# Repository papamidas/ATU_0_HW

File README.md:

# ATU_0_HW

Antenna Tuning Unit for Radio Amateurs:

- LC- or CL-type antenna tuner, software selectable
- 256 capacitance values: 0..2.5 nF in steps of 10 pF
- 256 inductance values	- 256 inductance values: 0..15 µH in steps of 60 nH
- controlled by an Arduino Nano
- powered by a USB power bank
- low current consumption (25..45 mA) by using bistable relays
- remote control via Bluetooth
- simple user interface using the Android app "serial bluetooth terminal"
- 10 memory buttons for recalling setups for different frequency bands
- open source hardware, open source firmware

have fun!
73
papamidas (DM1CR)

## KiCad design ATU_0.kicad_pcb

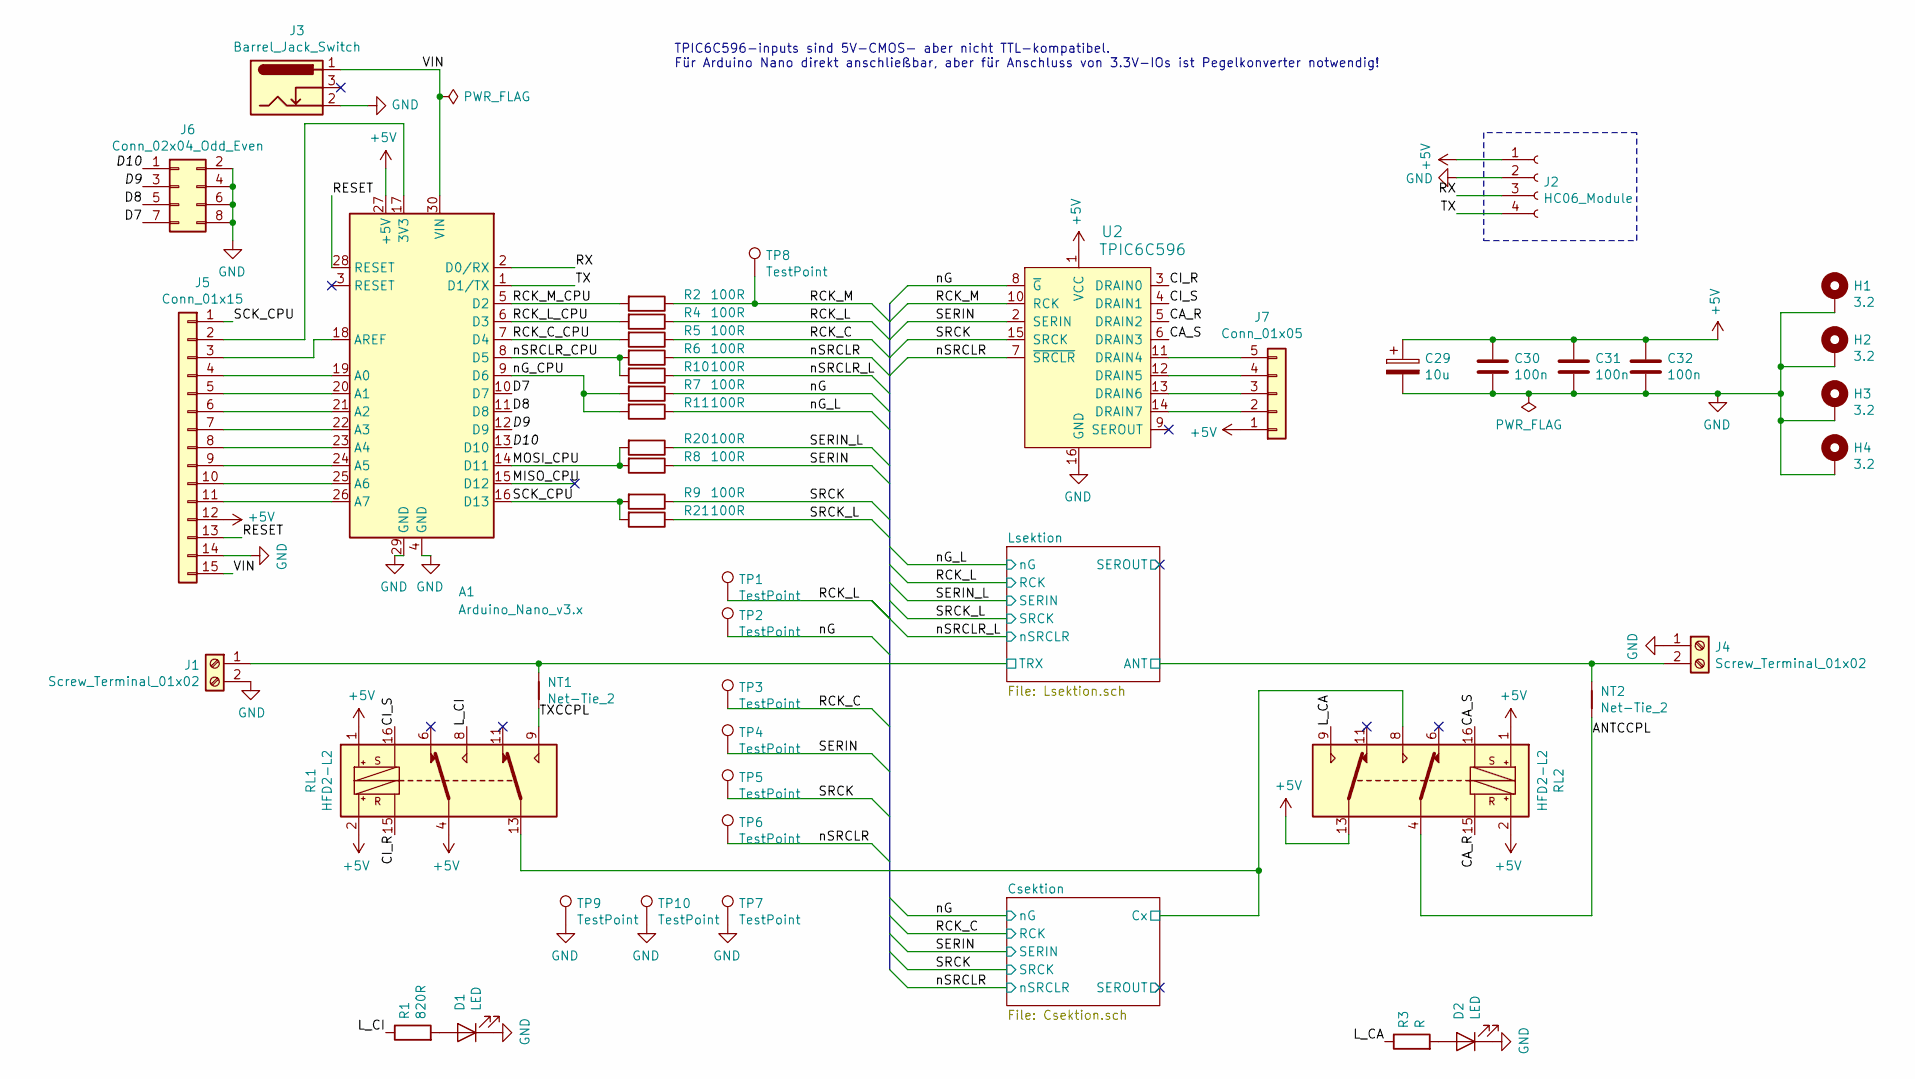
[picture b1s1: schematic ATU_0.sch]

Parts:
A1: Arduino_Nano_v3.x; Arduino_Nano_WithMountingHoles
C29: 10u; CP_Tantalum_Case-C_EIA-6032-28_Hand
C30, C31, C32: 100n; C_0805_HandSoldering
D1, D2: LED; D_0805
H1, H2, H3, H4: 3.2; MountingHole_3.2mm_M3_DIN965_Pad
J1, J4: Screw_Terminal_01x02; TerminalBlock_bornier-2_P5.08mm
J2: HC06_Module; Socket_Strip_Straight_1x04_Pitch2.54mm
J3: Barrel_Jack_Switch; Barrel_Jack_5.5mmODx2.1mmID_PJ-202A
J5: Conn_01x15; PinHeader_1x15_P2.54mm_Vertical
J6: Conn_02x04_Odd_Even; PinHeader_2x04_P2.54mm_Vertical
J7: Conn_01x05; PinHeader_1x05_P2.54mm_Vertical
NT1, NT2: Net-Tie_2; NetTie-2_SMD_Pad2.0mm
R1: 820R; R_0805_HandSoldering
R2, R4, R5, R6, R7, R8, R9, R10, R11, R20, R21: 100R; R_0805_HandSoldering
R3: R; R_0805_HandSoldering
RL1, RL2: HFD2-L2
TP1, TP2, TP3, TP4, TP5, TP6, TP7, TP8, TP9, TP10: TestPoint; PinHeader_1x01_P2.54mm_Vertical
U2: TPIC6C596; SOIC-16_W3.90mm; MPN TPIC6C596; Digi-Key_PN Mouser TPIC6C596DRQ1

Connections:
+5V: A1.27 (+5V), C29.1, C30.1, C31.1, C32.1, J2.1, J5.12, J7.1, RL1.1, RL1.2, RL1.4, RL2.1, RL2.2, RL2.13, U2.1 (VCC); also elsewhere on the board
/ANTCCPL: NT2.2, RL2.4
/CA_R: RL2.15, U2.5 (DRAIN2)
/CA_S: RL2.16, U2.6 (DRAIN3)
/CI_R: RL1.15, U2.3 (DRAIN0)
/CI_S: RL1.16, U2.4 (DRAIN1)
/Csektion/Cx: RL1.13, RL2.8; also elsewhere on the board
/D7: A1.10 (D7), J6.7
/D8: A1.11 (D8), J6.5
/D9: A1.12 (D9), J6.3
/D10: A1.13 (D10), J6.1
/L_CA: R3.1, RL2.9
/L_CI: R1.1, RL1.8
/Lsektion/ANT: J4.2, NT2.1; also elsewhere on the board
/Lsektion/TRX: J1.1, NT1.1; also elsewhere on the board
/MISO_CPU: A1.15 (D12)
/MOSI_CPU: A1.14 (D11), R8.2, R20.2
/RCK_C: R5.1, TP3.1; also elsewhere on the board
/RCK_C_CPU: A1.7 (D4), R5.2
/RCK_L: R4.1, TP1.1; also elsewhere on the board
/RCK_L_CPU: A1.6 (D3), R4.2
/RCK_M: R2.1, TP8.1, U2.10 (RCK)
/RCK_M_CPU: A1.5 (D2), R2.2
/RESET: A1.28 (RESET), J5.13
/RX: A1.2 (D0/RX), J2.3
/SCK_CPU: A1.16 (D13), J5.1, R9.2, R21.2
/SERIN: R8.1, TP4.1, U2.2 (SERIN); also elsewhere on the board
/SERIN_L: R20.1; also elsewhere on the board
/SRCK: R9.1, TP5.1, U2.15 (SRCK); also elsewhere on the board
/SRCK_L: R21.1; also elsewhere on the board
/TX: A1.1 (D1/TX), J2.4
/TXCCPL: NT1.2, RL1.9
/VIN: A1.30 (VIN), J3.1, J5.15
/nG: R7.1, TP2.1, U2.8 (~G); also elsewhere on the board
/nG_CPU: A1.9 (D6), R7.2, R11.2
/nG_L: R11.1; also elsewhere on the board
/nSRCLR: R6.1, TP6.1, U2.7 (~SRCLR); also elsewhere on the board
/nSRCLR_CPU: A1.8 (D5), R6.2, R10.2
/nSRCLR_L: R10.1; also elsewhere on the board
GND: A1.4 (GND), A1.29 (GND), C29.2, C30.2, C31.2, C32.2, D1.1 (K), D2.1 (K), H1.1, H2.1, H3.1, H4.1, J1.2, J2.2, J3.2, J4.1, J5.14, J6.2, J6.4, J6.6, J6.8, TP7.1, TP9.1, TP10.1, U2.16 (GND); also elsewhere on the board
unnamed: A1.17 (3V3), J5.2
unnamed: A1.18 (AREF), J5.3
unnamed: A1.19 (A0), J5.4
unnamed: A1.20 (A1), J5.5
unnamed: A1.21 (A2), J5.6
unnamed: A1.22 (A3), J5.7
unnamed: A1.23 (A4), J5.8
unnamed: A1.24 (A5), J5.9
unnamed: A1.25 (A6), J5.10
unnamed: A1.26 (A7), J5.11
unnamed: D1.2 (A), R1.2
unnamed: D2.2 (A), R3.2
unnamed: J7.2, U2.14 (DRAIN7)
unnamed: J7.3, U2.13 (DRAIN6)
unnamed: J7.4, U2.12 (DRAIN5)
unnamed: J7.5, U2.11 (DRAIN4)

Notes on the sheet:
TPIC6C596-inputs sind 5V-CMOS- aber nicht TTL-kompatibel. Für Arduino Nano direkt anschließbar, aber für Anschluss von 3.3V-IOs ist Pegelkonverter notwendig!

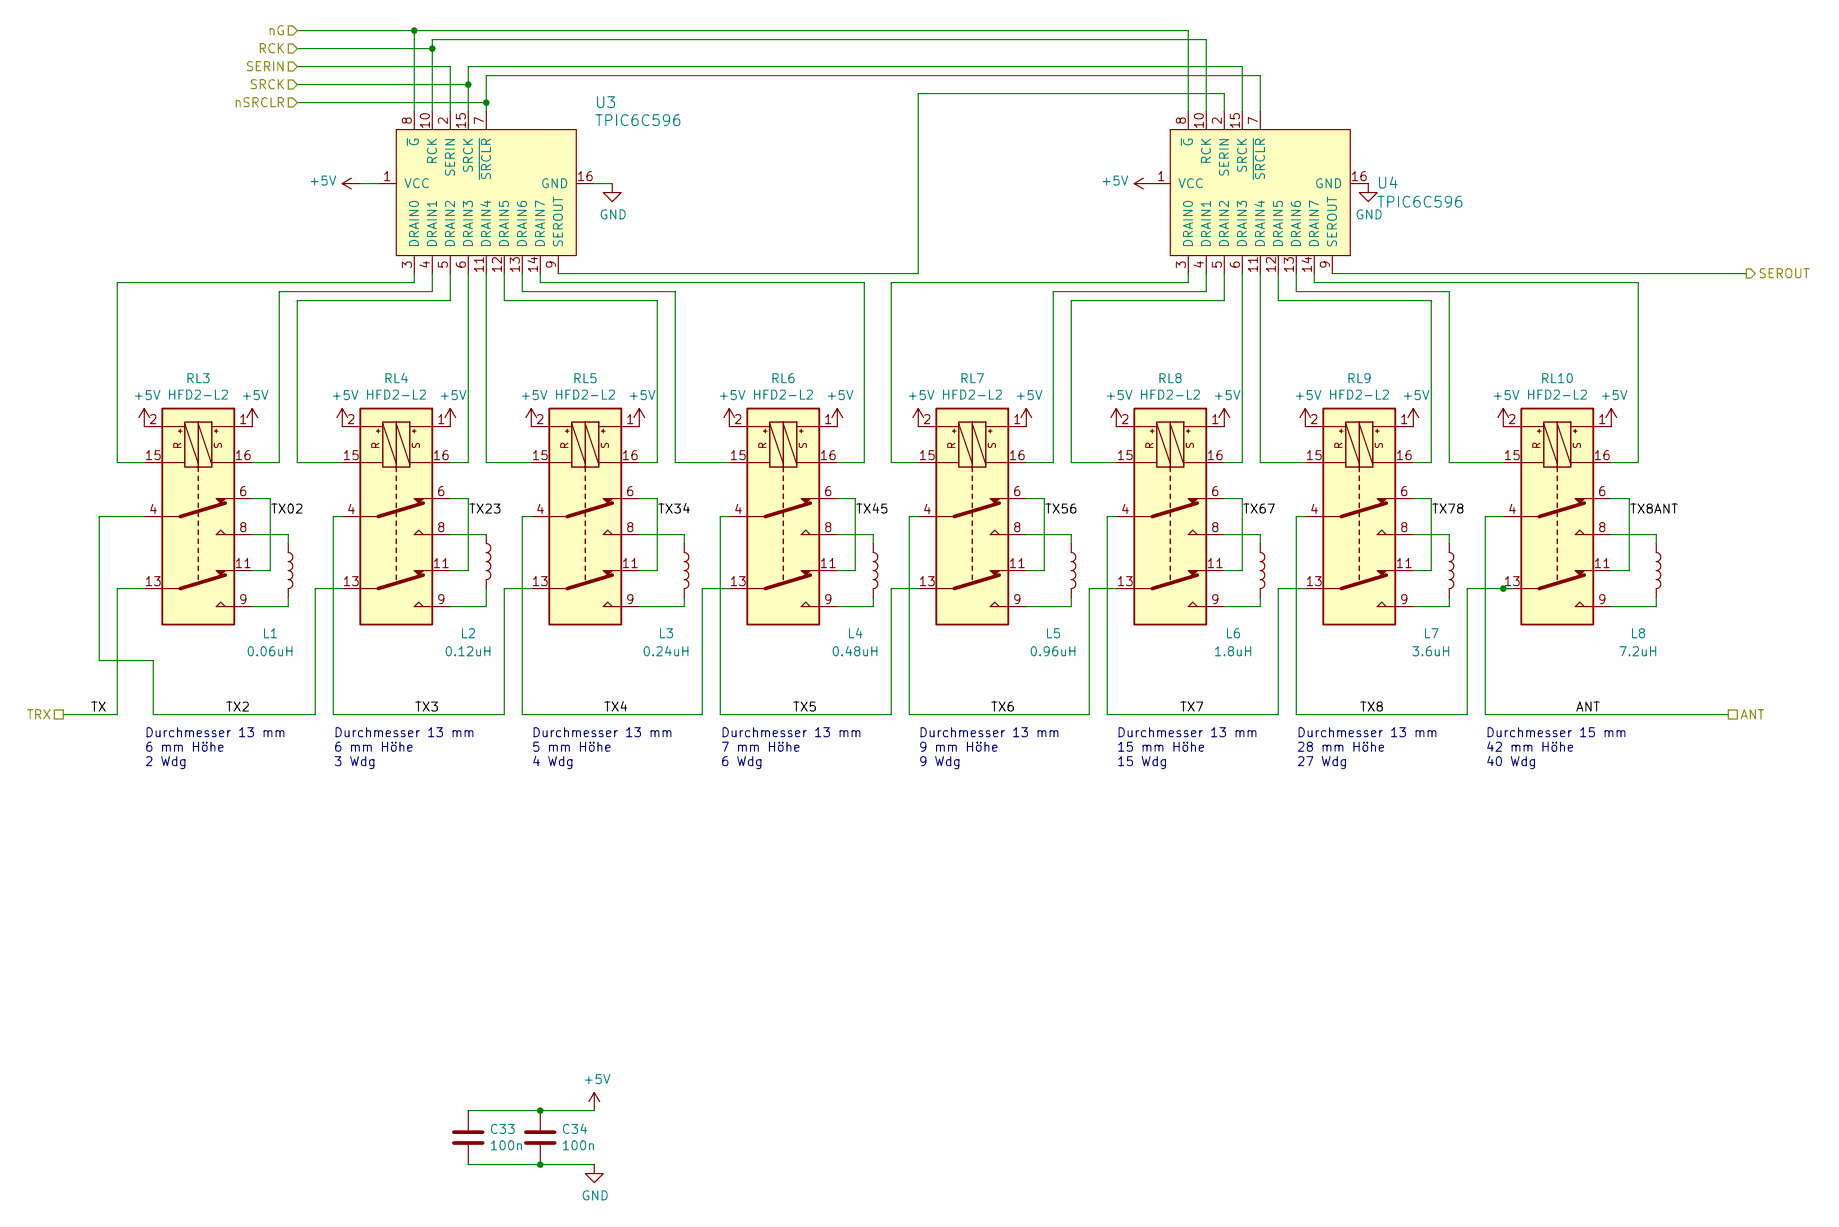
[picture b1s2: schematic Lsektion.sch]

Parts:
C33, C34: 100n; C_0805_HandSoldering
L1: 0.06uH; Aircoil_7_62_d15
L2: 0.12uH; Aircoil_7_62_d15
L3: 0.24uH; Aircoil_7_62_d15
L4: 0.48uH; Aircoil_7_62_d15
L5: 0.96uH; Aircoil_10_16_d15
L6: 1.8uH; Aircoil_15_24_d15
L7: 3.6uH; Aircoil_27_94_d15
L8: 7.2uH; Aircoil_43_18_d17
RL3, RL4, RL5, RL6, RL7, RL8, RL9, RL10: HFD2-L2
U3, U4: TPIC6C596; SOIC-16_W3.90mm; MPN TPIC6C596; Digi-Key_PN Mouser TPIC6C596DRQ1

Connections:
+5V: C33.1, C34.1, RL3.1, RL3.2, RL4.1, RL4.2, RL5.1, RL5.2, RL6.1, RL6.2, RL7.1, RL7.2, RL8.1, RL8.2, RL9.1, RL9.2, RL10.1, RL10.2, U3.1 (VCC), U4.1 (VCC); also elsewhere on the board
/Lsektion/ANT: RL10.4; also elsewhere on the board
/Lsektion/SEROUT: U4.9 (SEROUT)
/Lsektion/TRX: RL3.13; also elsewhere on the board
/Lsektion/TX2: RL3.4, RL4.13
/Lsektion/TX02: RL3.6, RL3.11
/Lsektion/TX3: RL4.4, RL5.13
/Lsektion/TX4: RL5.4, RL6.13
/Lsektion/TX5: RL6.4, RL7.13
/Lsektion/TX6: RL7.4, RL8.13
/Lsektion/TX7: RL8.4, RL9.13
/Lsektion/TX8: RL9.4, RL10.13
/Lsektion/TX8ANT: RL10.6, RL10.11
/Lsektion/TX23: RL4.6, RL4.11
/Lsektion/TX34: RL5.6, RL5.11
/Lsektion/TX45: RL6.6, RL6.11
/Lsektion/TX56: RL7.6, RL7.11
/Lsektion/TX67: RL8.6, RL8.11
/Lsektion/TX78: RL9.6, RL9.11
/RCK_L: U3.10 (RCK), U4.10 (RCK); also elsewhere on the board
/SERIN_L: U3.2 (SERIN); also elsewhere on the board
/SRCK_L: U3.15 (SRCK), U4.15 (SRCK); also elsewhere on the board
/nG_L: U3.8 (~G), U4.8 (~G); also elsewhere on the board
/nSRCLR_L: U3.7 (~SRCLR), U4.7 (~SRCLR); also elsewhere on the board
GND: C33.2, C34.2, U3.16 (GND), U4.16 (GND); also elsewhere on the board
unnamed: L1.1, RL3.8
unnamed: L1.2, RL3.9
unnamed: L2.1, RL4.8
unnamed: L2.2, RL4.9
unnamed: L3.1, RL5.8
unnamed: L3.2, RL5.9
unnamed: L4.1, RL6.8
unnamed: L4.2, RL6.9
unnamed: L5.1, RL7.8
unnamed: L5.2, RL7.9
unnamed: L6.1, RL8.8
unnamed: L6.2, RL8.9
unnamed: L7.1, RL9.8
unnamed: L7.2, RL9.9
unnamed: L8.1, RL10.8
unnamed: L8.2, RL10.9
unnamed: RL3.15, U3.3 (DRAIN0)
unnamed: RL3.16, U3.4 (DRAIN1)
unnamed: RL4.15, U3.5 (DRAIN2)
unnamed: RL4.16, U3.6 (DRAIN3)
unnamed: RL5.15, U3.11 (DRAIN4)
unnamed: RL5.16, U3.12 (DRAIN5)
unnamed: RL6.15, U3.13 (DRAIN6)
unnamed: RL6.16, U3.14 (DRAIN7)
unnamed: RL7.15, U4.3 (DRAIN0)
unnamed: RL7.16, U4.4 (DRAIN1)
unnamed: RL8.15, U4.5 (DRAIN2)
unnamed: RL8.16, U4.6 (DRAIN3)
unnamed: RL9.15, U4.11 (DRAIN4)
unnamed: RL9.16, U4.12 (DRAIN5)
unnamed: RL10.15, U4.13 (DRAIN6)
unnamed: RL10.16, U4.14 (DRAIN7)
unnamed: U3.9 (SEROUT), U4.2 (SERIN)

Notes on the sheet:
Durchmesser 13 mm 6 mm Höhe 2 Wdg
Durchmesser 13 mm 6 mm Höhe 3 Wdg
Durchmesser 13 mm 5 mm Höhe 4 Wdg
Durchmesser 13 mm 7 mm Höhe 6 Wdg
Durchmesser 13 mm 9 mm Höhe 9 Wdg
Durchmesser 13 mm 15 mm Höhe 15 Wdg
Durchmesser 13 mm 28 mm Höhe 27 Wdg
Durchmesser 15 mm 42 mm Höhe 40 Wdg

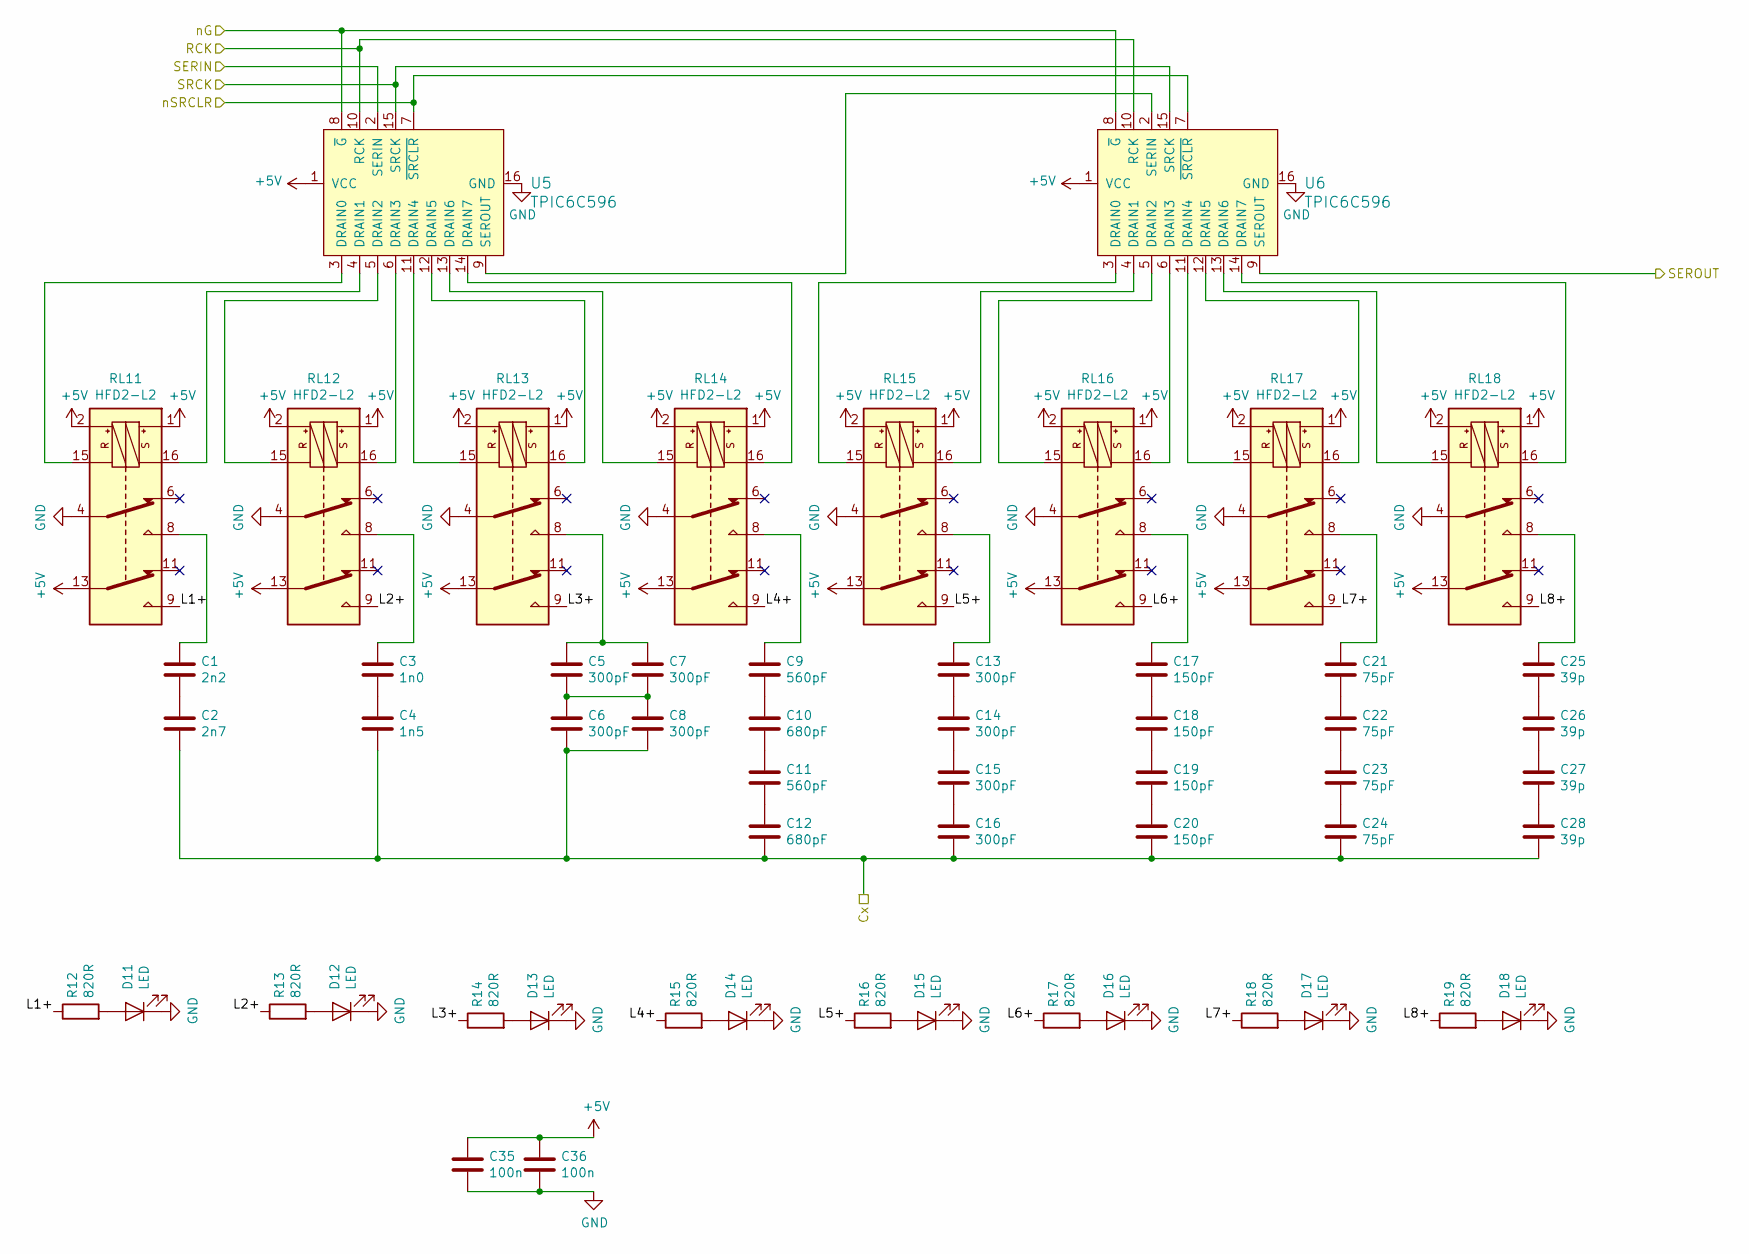
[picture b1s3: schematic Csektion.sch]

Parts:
C1: 2n2; C_1210_HandSoldering
C2: 2n7; C_1210_HandSoldering
C3: 1n0; C_1210_HandSoldering
C4: 1n5; C_1210_HandSoldering
C5, C6, C7, C8, C13, C14, C15, C16: 300pF; C_1210_HandSoldering
C9, C11: 560pF; C_1210_HandSoldering
C10, C12: 680pF; C_1210_HandSoldering
C17, C18, C19, C20: 150pF; C_1210_HandSoldering
C21, C22, C23, C24: 75pF; C_1210_HandSoldering
C25, C26, C27, C28: 39p; C_1210_HandSoldering
C35, C36: 100n; C_0805_HandSoldering
D11, D12, D13, D14, D15, D16, D17, D18: LED; D_0805
R12, R13, R14, R15, R16, R17, R18, R19: 820R; R_0805_HandSoldering
RL11, RL12, RL13, RL14, RL15, RL16, RL17, RL18: HFD2-L2
U5, U6: TPIC6C596; SOIC-16_W3.90mm; MPN TPIC6C596; Digi-Key_PN Mouser TPIC6C596DRQ1

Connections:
+5V: C35.1, C36.1, RL11.1, RL11.2, RL11.13, RL12.1, RL12.2, RL12.13, RL13.1, RL13.2, RL13.13, RL14.1, RL14.2, RL14.13, RL15.1, RL15.2, RL15.13, RL16.1, RL16.2, RL16.13, RL17.1, RL17.2, RL17.13, RL18.1, RL18.2, RL18.13, U5.1 (VCC), U6.1 (VCC); also elsewhere on the board
/Csektion/Cx: C2.2, C4.2, C6.2, C8.2, C12.2, C16.2, C20.2, C24.2, C28.2; also elsewhere on the board
/Csektion/L1+: R12.1, RL11.9
/Csektion/L2+: R13.1, RL12.9
/Csektion/L3+: R14.1, RL13.9
/Csektion/L4+: R15.1, RL14.9
/Csektion/L5+: R16.1, RL15.9
/Csektion/L6+: R17.1, RL16.9
/Csektion/L7+: R18.1, RL17.9
/Csektion/L8+: R19.1, RL18.9
/Csektion/SEROUT: U6.9 (SEROUT)
/RCK_C: U5.10 (RCK), U6.10 (RCK); also elsewhere on the board
/SERIN: U5.2 (SERIN); also elsewhere on the board
/SRCK: U5.15 (SRCK), U6.15 (SRCK); also elsewhere on the board
/nG: U5.8 (~G), U6.8 (~G); also elsewhere on the board
/nSRCLR: U5.7 (~SRCLR), U6.7 (~SRCLR); also elsewhere on the board
GND: C35.2, C36.2, D11.1 (K), D12.1 (K), D13.1 (K), D14.1 (K), D15.1 (K), D16.1 (K), D17.1 (K), D18.1 (K), RL11.4, RL12.4, RL13.4, RL14.4, RL15.4, RL16.4, RL17.4, RL18.4, U5.16 (GND), U6.16 (GND); also elsewhere on the board
unnamed: C1.1, RL11.8
unnamed: C1.2, C2.1
unnamed: C3.1, RL12.8
unnamed: C3.2, C4.1
unnamed: C5.1, C7.1, RL13.8
unnamed: C5.2, C6.1, C7.2, C8.1
unnamed: C9.1, RL14.8
unnamed: C9.2, C10.1
unnamed: C10.2, C11.1
unnamed: C11.2, C12.1
unnamed: C13.1, RL15.8
unnamed: C13.2, C14.1
unnamed: C14.2, C15.1
unnamed: C15.2, C16.1
unnamed: C17.1, RL16.8
unnamed: C17.2, C18.1
unnamed: C18.2, C19.1
unnamed: C19.2, C20.1
unnamed: C21.1, RL17.8
unnamed: C21.2, C22.1
unnamed: C22.2, C23.1
unnamed: C23.2, C24.1
unnamed: C25.1, RL18.8
unnamed: C25.2, C26.1
unnamed: C26.2, C27.1
unnamed: C27.2, C28.1
unnamed: D11.2 (A), R12.2
unnamed: D12.2 (A), R13.2
unnamed: D13.2 (A), R14.2
unnamed: D14.2 (A), R15.2
unnamed: D15.2 (A), R16.2
unnamed: D16.2 (A), R17.2
unnamed: D17.2 (A), R18.2
unnamed: D18.2 (A), R19.2
unnamed: RL11.15, U5.3 (DRAIN0)
unnamed: RL11.16, U5.4 (DRAIN1)
unnamed: RL12.15, U5.5 (DRAIN2)
unnamed: RL12.16, U5.6 (DRAIN3)
unnamed: RL13.15, U5.11 (DRAIN4)
unnamed: RL13.16, U5.12 (DRAIN5)
unnamed: RL14.15, U5.13 (DRAIN6)
unnamed: RL14.16, U5.14 (DRAIN7)
unnamed: RL15.15, U6.3 (DRAIN0)
unnamed: RL15.16, U6.4 (DRAIN1)
unnamed: RL16.15, U6.5 (DRAIN2)
unnamed: RL16.16, U6.6 (DRAIN3)
unnamed: RL17.15, U6.11 (DRAIN4)
unnamed: RL17.16, U6.12 (DRAIN5)
unnamed: RL18.15, U6.13 (DRAIN6)
unnamed: RL18.16, U6.14 (DRAIN7)
unnamed: U5.9 (SEROUT), U6.2 (SERIN)

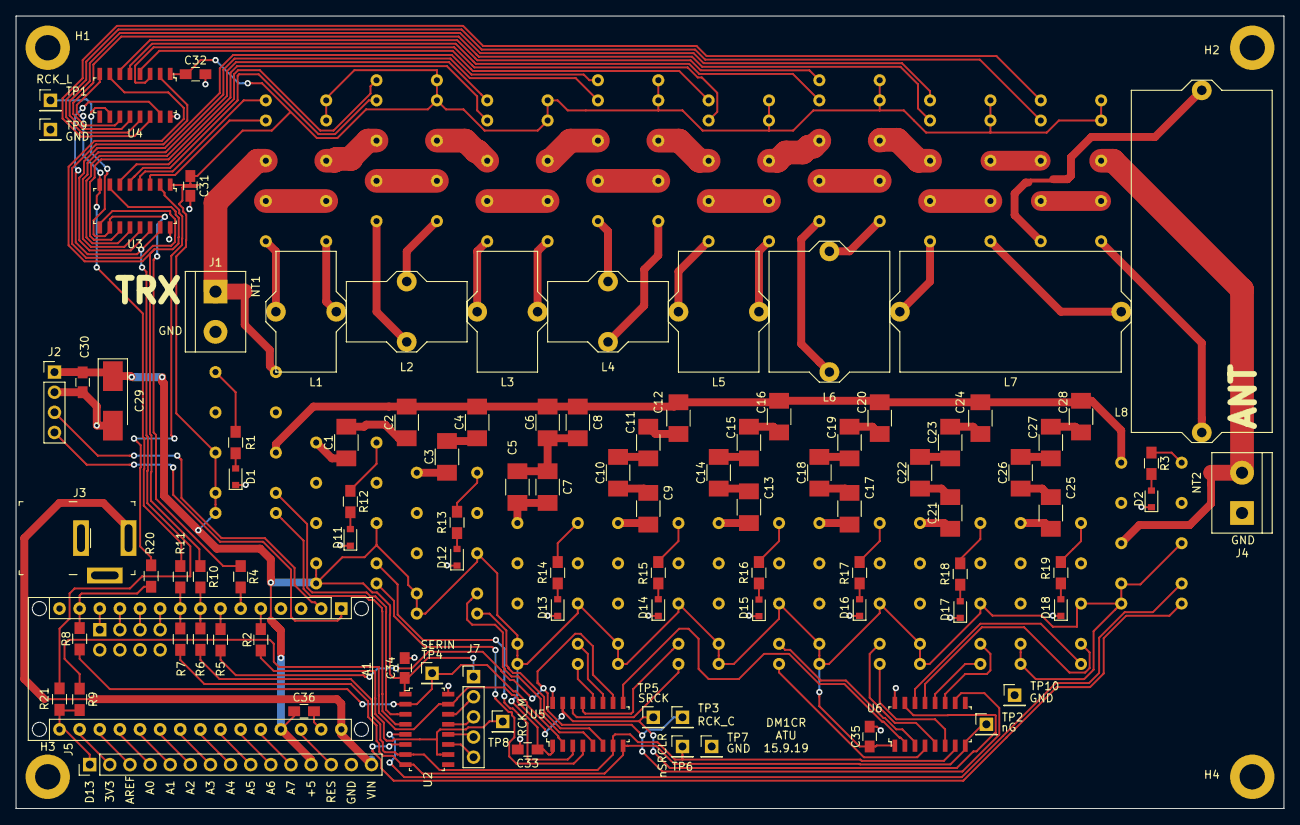
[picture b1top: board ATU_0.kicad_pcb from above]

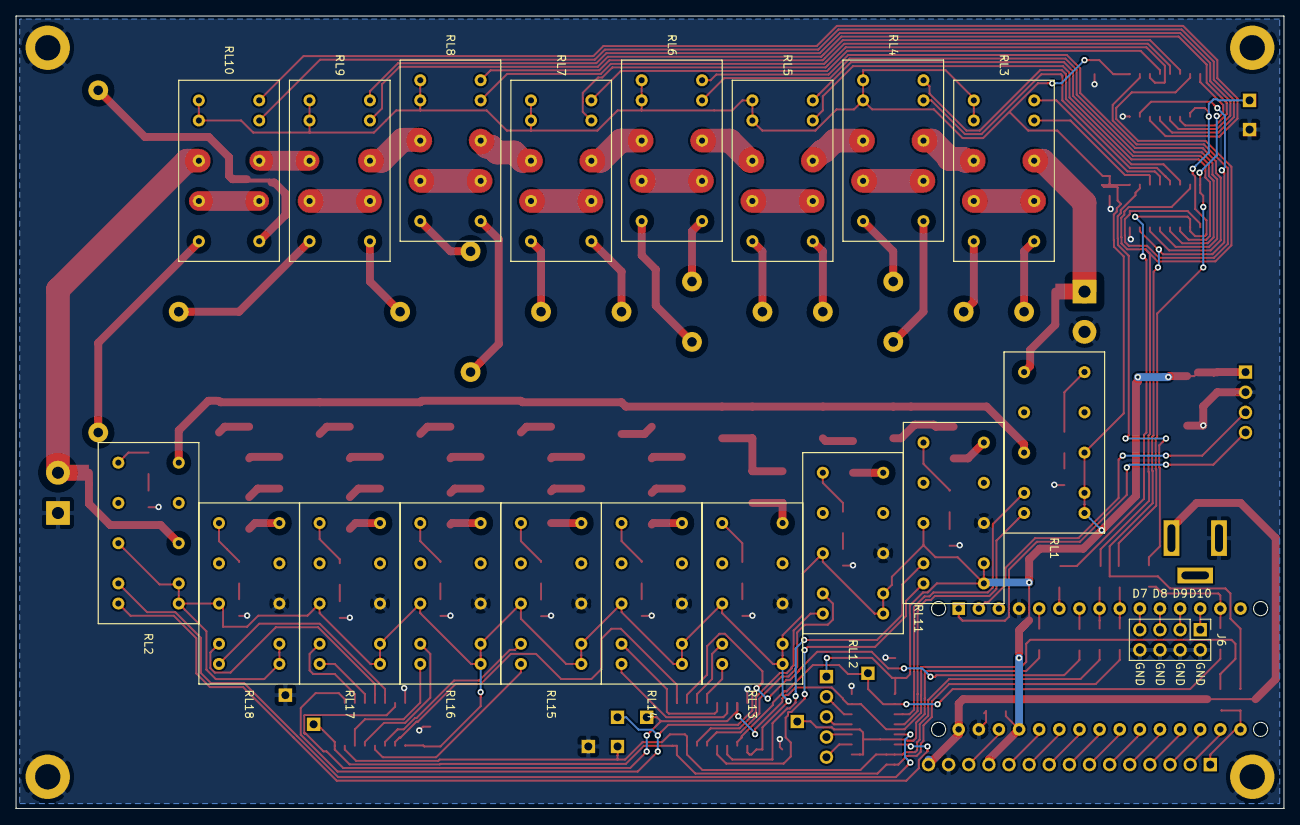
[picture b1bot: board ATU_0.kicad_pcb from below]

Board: 2 copper layers, 160.0 x 100.0 mm, 122 parts (19 on the bottom side), 162 nets.

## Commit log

2019-11-07 Pictures added
2019-11-10 new commit
2019-11-10 pics added again
